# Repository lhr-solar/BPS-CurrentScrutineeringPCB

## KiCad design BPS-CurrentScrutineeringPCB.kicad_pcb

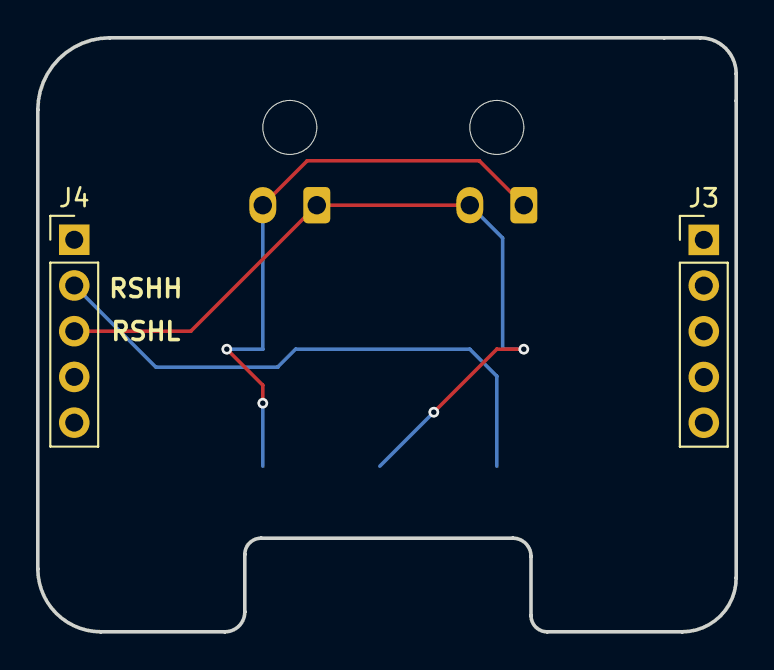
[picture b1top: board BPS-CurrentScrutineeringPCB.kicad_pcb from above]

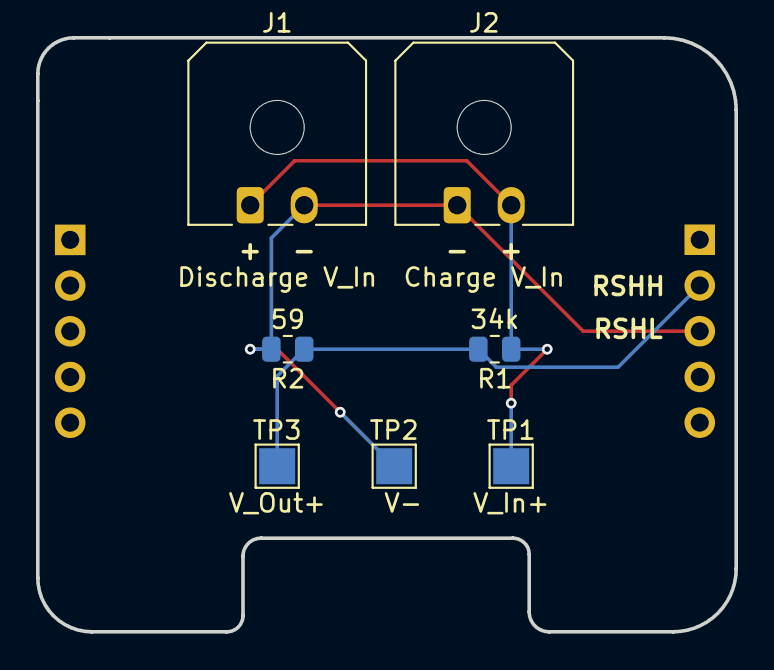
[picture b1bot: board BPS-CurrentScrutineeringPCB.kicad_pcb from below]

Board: 2 copper layers, 38.8 x 33.0 mm, 9 parts (7 on the bottom side), 3 nets.

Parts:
J1: Discharge V_In; Molex_Micro-Fit_3.0_43650-0200_1x02_P3.00mm_Horizontal
J2: Charge V_In; Molex_Micro-Fit_3.0_43650-0200_1x02_P3.00mm_Horizontal
J3, J4: Conn_01x05; PinHeader_1x05_P2.54mm_Vertical
R1: 34k; R_0805_2012Metric
R2: 59; R_0805_2012Metric
TP1: V_In+; TestPoint_Pad_2.0x2.0mm
TP2: V-; TestPoint_Pad_2.0x2.0mm
TP3: V_Out+; TestPoint_Pad_2.0x2.0mm

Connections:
/V-: J1.2, J2.1, J4.3, R2.2, TP2.1
/V_In+: J1.1, J2.2, R1.1, TP1.1
/V_Out+: J4.2, R1.2, R2.1, TP3.1

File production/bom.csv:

Designator,Footprint,Quantity,Value,LCSC Part #
J1,Molex_Micro-Fit_3.0_43650-0200_1x02_P3.00mm_Horizontal,1,Discharge V_In,
J2,Molex_Micro-Fit_3.0_43650-0200_1x02_P3.00mm_Horizontal,1,Charge V_In,
"J3, J4",PinHeader_1x05_P2.54mm_Vertical,2,Conn_01x05,
R1,0805,1,34k,
R2,0805,1,59,
TP1,TestPoint_Pad_2.0x2.0mm,1,V_In+,
TP2,TestPoint_Pad_2.0x2.0mm,1,V-,
TP3,TestPoint_Pad_2.0x2.0mm,1,V_Out+,

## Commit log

2025-06-14 safety verified
2025-06-14 poop
2025-06-17 Use .gitignore from master
2025-06-17 safey verified
